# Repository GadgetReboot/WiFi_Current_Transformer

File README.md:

# WiFi_Current_Transformer
ESP8266 based current transformer interface using SCT-013<br><br>
<br><br>

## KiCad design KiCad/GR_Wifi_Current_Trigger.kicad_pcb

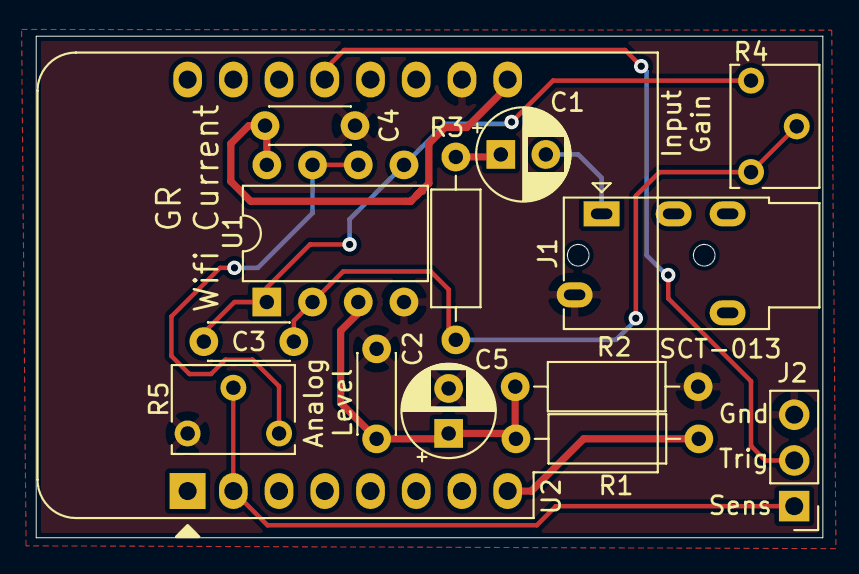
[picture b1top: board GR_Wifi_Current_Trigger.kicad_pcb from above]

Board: 2 copper layers, 43.7 x 27.9 mm, 14 parts (0 on the bottom side), 11 nets.

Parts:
C1: 10uF; CP_Radial_D5.0mm_P2.50mm
C2, C4: 100nF; C_Disc_D4.3mm_W1.9mm_P5.00mm
C3: DNI; C_Disc_D4.3mm_W1.9mm_P5.00mm
C5: DNI; CP_Radial_D5.0mm_P2.50mm
J1: 3.5mm Jack; Jack_3.5mm_PJ320E_Horizontal
J2: Conn_01x03; PinHeader_1x03_P2.54mm_Vertical
R1, R2: 47K; R_Axial_DIN0207_L6.3mm_D2.5mm_P10.16mm_Horizontal
R3: 1K; R_Axial_DIN0207_L6.3mm_D2.5mm_P10.16mm_Horizontal
R4, R5: 25K; Potentiometer_Vishay_T73XX_Horizontal
U1: LM358; DIP-8_W7.62mm
U2: WeMos_D1_mini; WEMOS_D1_mini_light

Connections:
+3V3: R1.1, U2.8
+5V: C4.1, U1.8, U2.9
/Sensor: J2.1, R5.2, U2.2
/Triggered: J2.2, U2.13
GNDREF: C2.2, C4.2, C5.2, J1.S, J2.3, R2.2, R5.1, U1.4, U2.10
unnamed: C1.1, R3.2
unnamed: C1.2, J1.T
unnamed: C2.1, C5.1, R1.2, R2.1, U1.3
unnamed: C3.1, R4.1, U1.1, U1.5
unnamed: C3.2, R3.1, R4.2, R4.3, U1.2
unnamed: R5.3, U1.6, U1.7
